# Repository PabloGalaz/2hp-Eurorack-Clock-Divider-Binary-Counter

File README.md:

# 2hp-Eurorack-Clock-Divider-Binary-Counter

Slim CD4024-based Eurorack Clock Divider/Binary Counter derived from a schematic by PolyKit (https://polykit.rocks/eurorack-clock-divider-module-modular-synth-diy/), with the following differences:

- 2hp (instead of 4hp)
- Mostly SMD components (0603)
- Added /128 output
- Added LED for clock input (through-hole, bent; watch video)
- Only one board

The PCB layout was inspired by the PCB layout of Uncertainty, by OAM (https://github.com/oamodular/uncertainty.git)

Version 2 is the only one that has been manufactured and tested. This version has a footprint error that can be fixed by carefully bending the legs of the five MMBT3904 transistors (SOT-23-3) and soldering them upside down (!). It's easier than it sounds, and it will work. Version 3 has that error fixed, but has not been tested yet.

BUILD THIS AT YOUR OWN RISK. FILES PROVIDED "AS IS", WITHOUT WARRANTY OF ANY KIND.

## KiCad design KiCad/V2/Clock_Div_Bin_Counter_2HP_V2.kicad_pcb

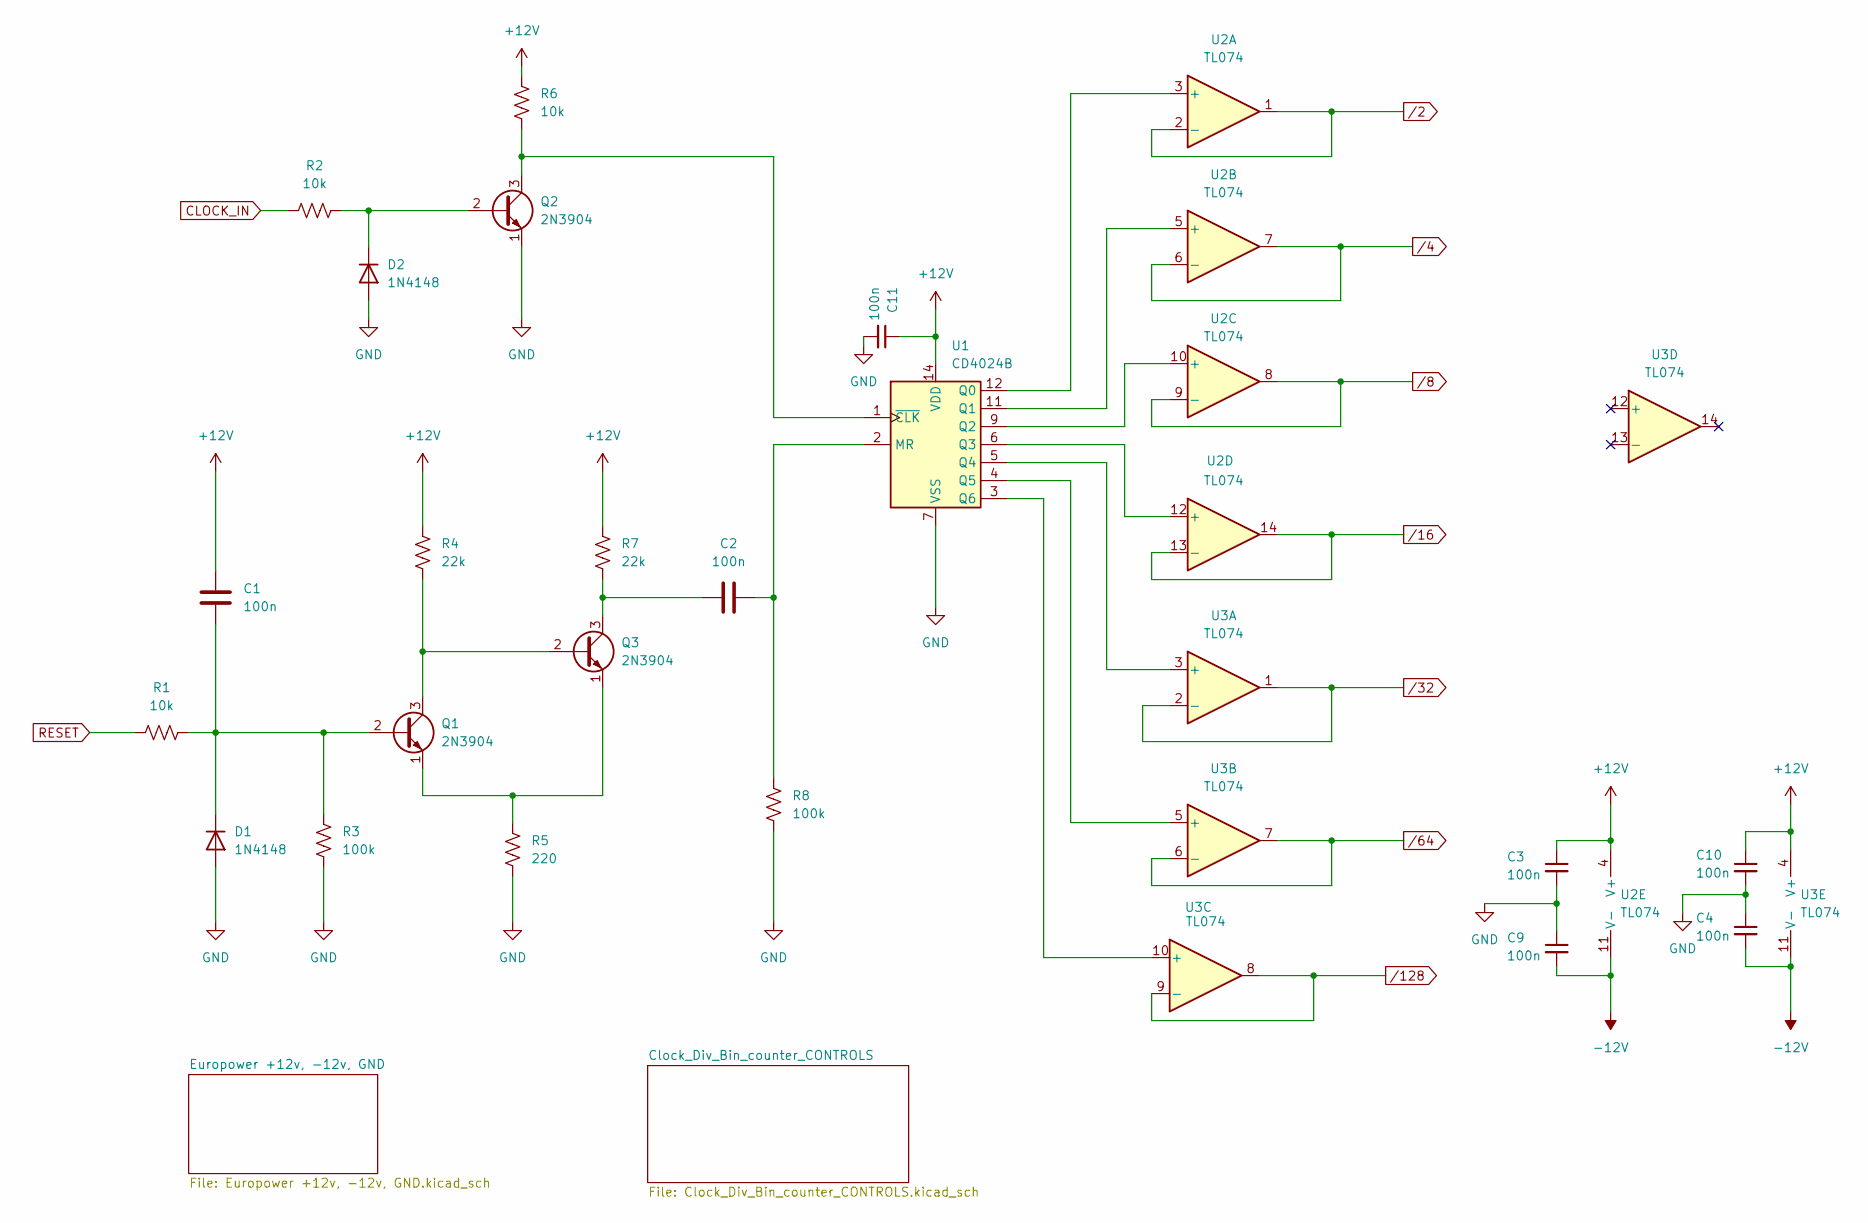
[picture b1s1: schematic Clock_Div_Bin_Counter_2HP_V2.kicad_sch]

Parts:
C1, C2, C3, C4, C9, C10, C11: 100n; C_0603_1608Metric
D1, D2: 1N4148; Nexperia_CFP3_SOD-123W
Q1, Q2, Q3: 2N3904; SOT-23
R1, R2, R6: 10k; R_0603
R3, R8: 100k; R_0603
R4, R7: 22k; R_0603
R5: 220; R_0603
U1: CD4024B; SOIC-14_3.9x8.7mm_P1.27mm
U2, U3: TL074; SOIC-14_3.9x8.7mm_P1.27mm

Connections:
+12V: C1.1, C3.1, C10.1, C11.1, R4.2, R6.2, R7.2, U1.14 (VDD), U2.4 (V+), U3.4 (V+); also elsewhere on the board
-12V: C4.2, C9.2, U2.11 (V-), U3.11 (V-); also elsewhere on the board
CLOCK_IN: R2.1; also elsewhere on the board
GND: C3.2, C4.1, C9.1, C10.2, C11.2, D1.2 (A), D2.2 (A), Q2.1 (E), R3.1, R5.1, R8.1, U1.7 (VSS); also elsewhere on the board
unnamed: C1.2, D1.1 (K), Q1.2 (B), R1.2, R3.2
unnamed: D2.1 (K), Q2.2 (B), R2.2
unnamed: Q1.3 (C), Q3.2 (B), R4.1
unnamed: Q1.1 (E), Q3.1 (E), R5.2
unnamed: Q2.3 (C), R6.1, U1.1 (~CLK)
unnamed: C2.1, Q3.3 (C), R7.1
unnamed: C2.2, R8.2, U1.2 (MR)
unnamed: U1.12 (Q0), U2.3 (+)
unnamed: U1.11 (Q1), U2.5 (+)
unnamed: U1.9 (Q2), U2.10 (+)
unnamed: U1.6 (Q3), U2.12 (+)
unnamed: U1.5 (Q4), U3.3 (+)
unnamed: U1.4 (Q5), U3.5 (+)
unnamed: U1.3 (Q6), U3.10 (+)
RESET: R1.1; also elsewhere on the board
/2: U2.1, U2.2 (-); also elsewhere on the board
/4: U2.6 (-), U2.7; also elsewhere on the board
/8: U2.8, U2.9 (-); also elsewhere on the board
/16: U2.13 (-), U2.14; also elsewhere on the board
/32: U3.1, U3.2 (-); also elsewhere on the board
/64: U3.6 (-), U3.7; also elsewhere on the board
/128: U3.8, U3.9 (-); also elsewhere on the board

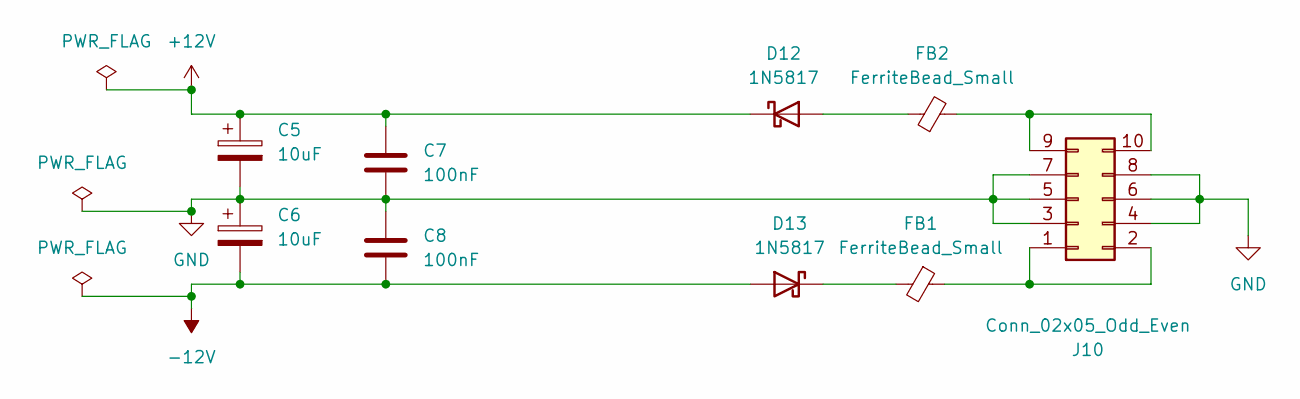
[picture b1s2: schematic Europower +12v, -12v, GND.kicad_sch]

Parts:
C5, C6: 10uF; CP_Radial_D5.0mm_P2.00mm
C7, C8: 100nF; C_0805_2012Metric_Pad1.18x1.45mm_HandSolder
D12, D13: 1N5817; D_SOD-323_HandSoldering
FB1, FB2: FerriteBead_Small; L_0805_2012Metric_Pad1.05x1.20mm_HandSolder
J10: Conn_02x05_Odd_Even; PinHeader_2x05_P2.54mm_Horizontal

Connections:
+12V: C5.1, C7.1, D12.1 (K); also elsewhere on the board
-12V: C6.2, C8.2, D13.2 (A); also elsewhere on the board
GND: C5.2, C6.1, C7.2, C8.1, J10.3, J10.4, J10.5, J10.6, J10.7, J10.8; also elsewhere on the board
unnamed: D12.2 (A), FB2.1
unnamed: D13.1 (K), FB1.2
unnamed: FB1.1, J10.1, J10.2
unnamed: FB2.2, J10.9, J10.10

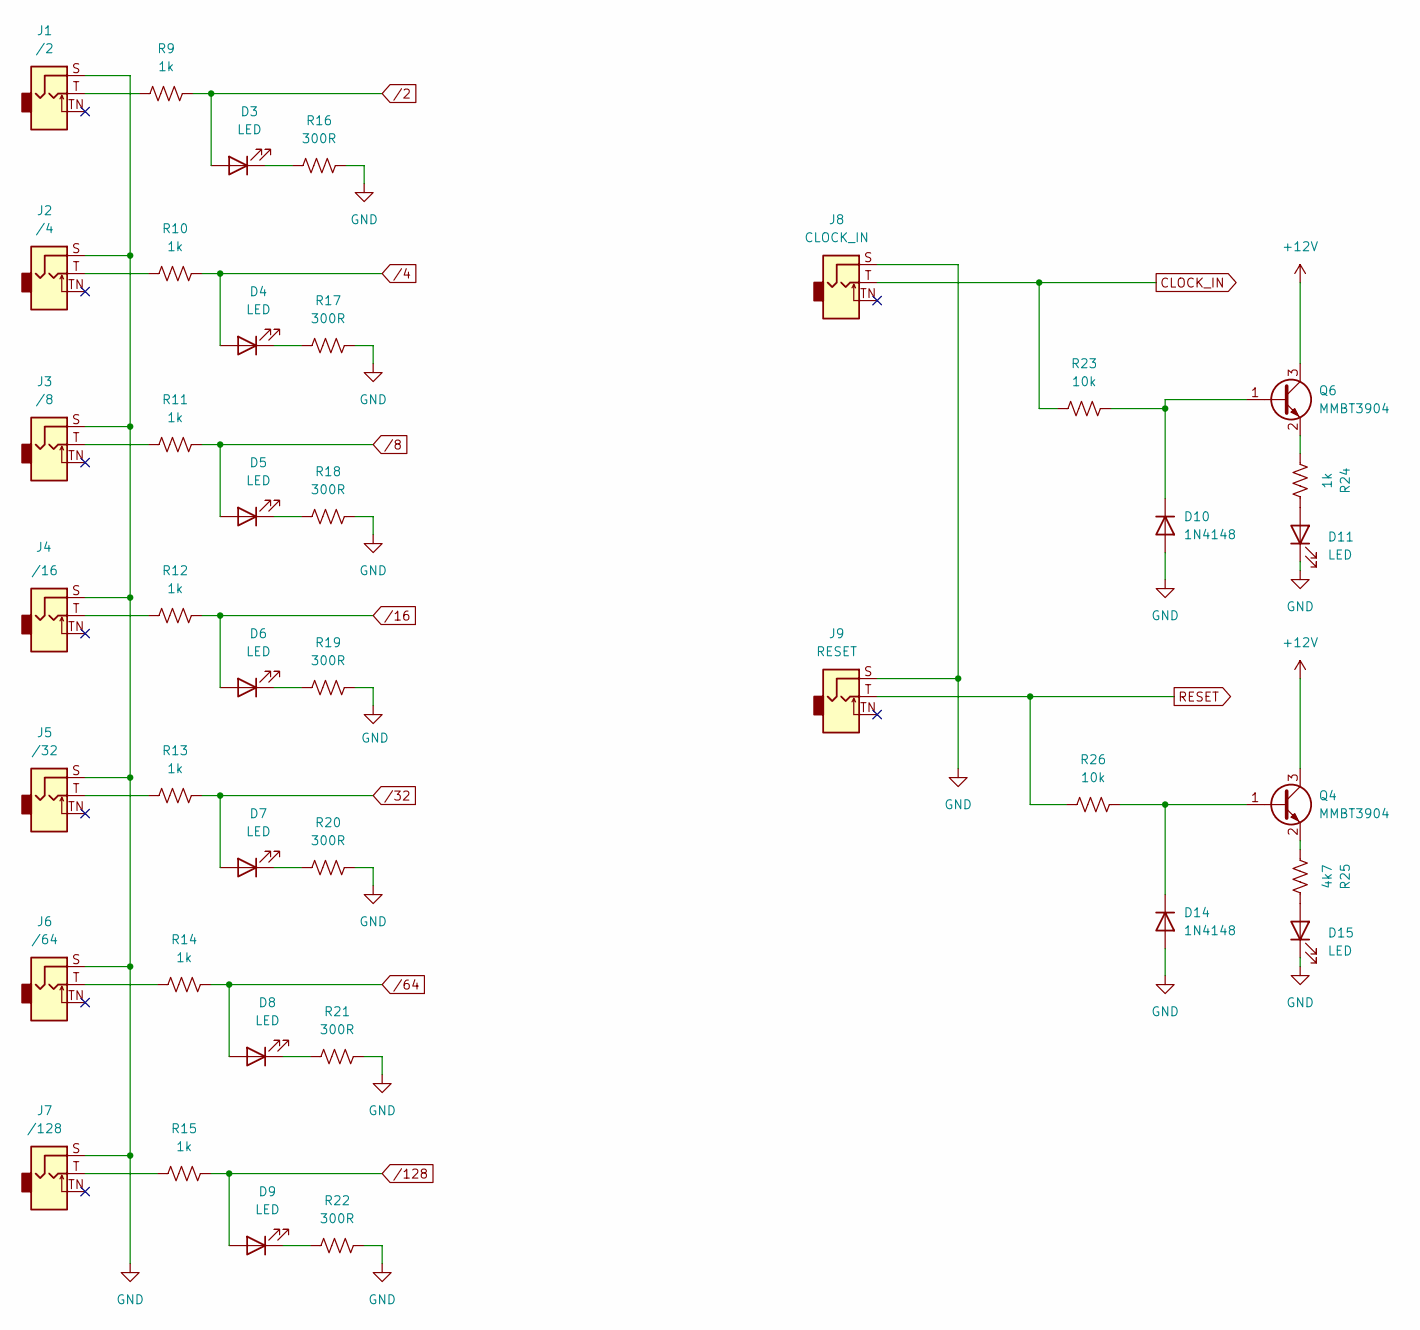
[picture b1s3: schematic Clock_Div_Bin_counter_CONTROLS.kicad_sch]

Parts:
D3, D4, D5, D6, D7, D8, D9, D15: LED; LED-SMD Red SideEmit Angle30 3x1mm -APPA3010SURCK
D10, D14: 1N4148; Nexperia_CFP3_SOD-123W
D11: LED; LED_3mm_C1A2_Polarity_Indicator
J1: /2; SWITCHCRAFT_35RASMT2AHNTRX; MPN 35RASMT2AHNTRX
J2: /4; SWITCHCRAFT_35RASMT2AHNTRX; MPN 35RASMT2AHNTRX
J3: /8; SWITCHCRAFT_35RASMT2AHNTRX; MPN 35RASMT2AHNTRX
J4: /16; SWITCHCRAFT_35RASMT2AHNTRX; MPN 35RASMT2AHNTRX
J5: /32; SWITCHCRAFT_35RASMT2AHNTRX; MPN 35RASMT2AHNTRX
J6: /64; SWITCHCRAFT_35RASMT2AHNTRX; MPN 35RASMT2AHNTRX
J7: /128; SWITCHCRAFT_35RASMT2AHNTRX; MPN 35RASMT2AHNTRX
J8: CLOCK_IN; SWITCHCRAFT_35RASMT2AHNTRX; MPN 35RASMT2AHNTRX
J9: RESET; SWITCHCRAFT_35RASMT2AHNTRX; MPN 35RASMT2AHNTRX
Q4, Q6: MMBT3904; SOT-23
R9, R10, R11, R12, R13, R14, R15, R24: 1k; R_0603
R16, R17, R18, R19, R20, R21, R22: 300R; R_0603
R23, R26: 10k; R_0603
R25: 4k7; R_0603

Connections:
+12V: Q4.3 (C), Q6.3 (C); also elsewhere on the board
CLOCK_IN: J8.T (Tip), R23.1; also elsewhere on the board
GND: D10.2 (A), D11.1 (K), D14.2 (A), D15.1 (K), J1.S (Sleeve), J2.S (Sleeve), J3.S (Sleeve), J4.S (Sleeve), J5.S (Sleeve), J6.S (Sleeve), J7.S (Sleeve), J8.S (Sleeve), J9.S (Sleeve), R16.2, R17.2, R18.2, R19.2, R20.2, R21.2, R22.2; also elsewhere on the board
unnamed: D3.1 (K), R16.1
unnamed: D4.1 (K), R17.1
unnamed: D5.1 (K), R18.1
unnamed: D6.1 (K), R19.1
unnamed: D7.1 (K), R20.1
unnamed: D8.1 (K), R21.1
unnamed: D9.1 (K), R22.1
unnamed: D11.2 (A), R24.2
unnamed: D15.2 (A), R25.2
unnamed: J1.T (Tip), R9.1
unnamed: J2.T (Tip), R10.1
unnamed: J3.T (Tip), R11.1
unnamed: J4.T (Tip), R12.1
unnamed: J5.T (Tip), R13.1
unnamed: J6.T (Tip), R14.1
unnamed: J7.T (Tip), R15.1
RESET: J9.T (Tip), R26.1; also elsewhere on the board
/2: D3.2 (A), R9.2; also elsewhere on the board
/4: D4.2 (A), R10.2; also elsewhere on the board
/8: D5.2 (A), R11.2; also elsewhere on the board
/16: D6.2 (A), R12.2; also elsewhere on the board
/32: D7.2 (A), R13.2; also elsewhere on the board
/64: D8.2 (A), R14.2; also elsewhere on the board
/128: D9.2 (A), R15.2; also elsewhere on the board

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
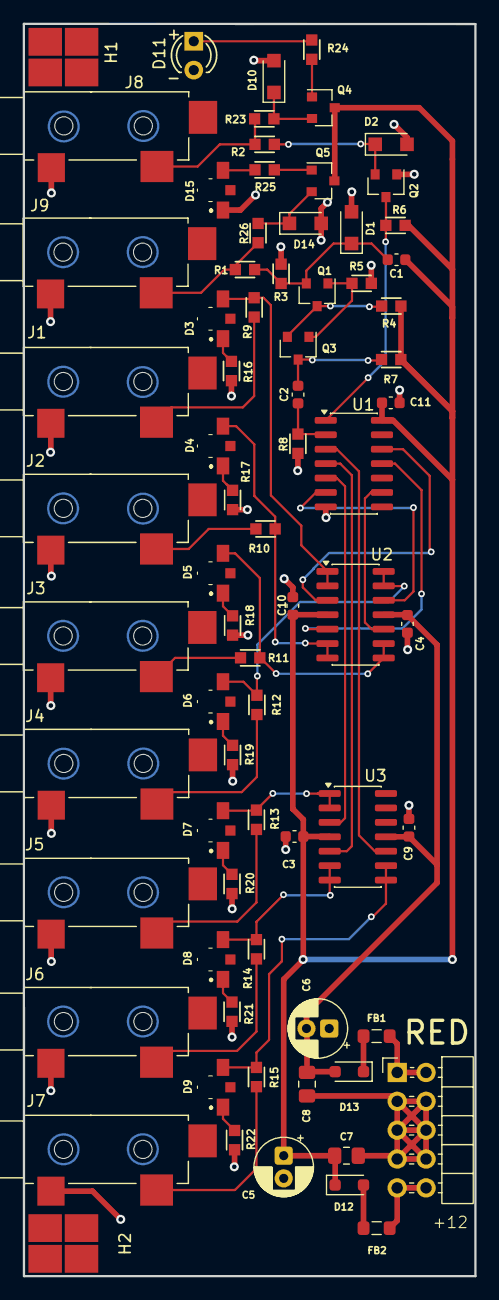
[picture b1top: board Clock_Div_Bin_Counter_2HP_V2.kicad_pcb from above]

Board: 2 copper layers, 39.8 x 110.2 mm, 74 parts (0 on the bottom side), 50 nets.

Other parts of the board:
H1, H2: Wurth 7466303; WP-SMRA_7466303
Q5: 2N3904; SOT-23

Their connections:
+12V: Q5.3 (C); also elsewhere on the board
